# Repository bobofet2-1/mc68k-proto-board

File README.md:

# mc68k-proto-board
Code and design of legacy MC68000 proto board

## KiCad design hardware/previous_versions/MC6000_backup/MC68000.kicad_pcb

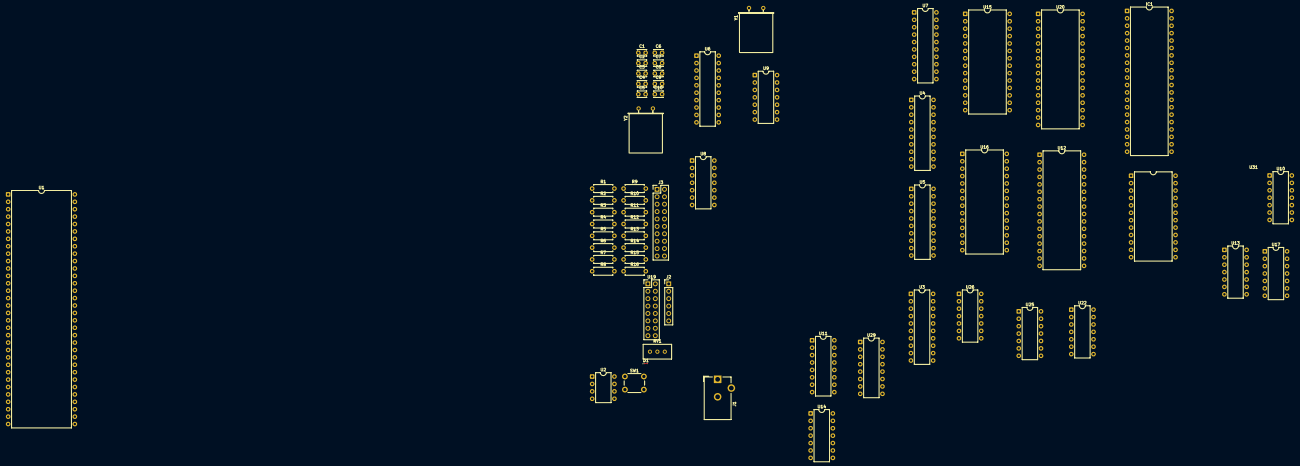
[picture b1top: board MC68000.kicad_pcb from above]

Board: 2 copper layers, 59 parts (0 on the bottom side), 146 nets, no tracks yet.

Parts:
C1: 10nF; C_Disc_D3.0mm_W2.0mm_P2.50mm
C2: 100n; C_Disc_D3.0mm_W2.0mm_P2.50mm
C3: 10n; C_Disc_D3.0mm_W2.0mm_P2.50mm
C4: 1u; C_Disc_D3.0mm_W2.0mm_P2.50mm
C5, C6, C7, C8: 15p; C_Disc_D3.0mm_W2.0mm_P2.50mm
C9: 10uF; C_Disc_D3.0mm_W2.0mm_P2.50mm
C10: 100nF; C_Disc_D3.0mm_W2.0mm_P2.50mm
D1: LED; LED_0201_0603Metric_Pad0.64x0.40mm_HandSolder
IC1: MC68681P; DIP-40_W15.24mm
J1: Conn_Coaxial_Power; BarrelJack_CUI_PJ-102AH_Horizontal
J2: FT232RL board; PinHeader_1x06_P2.54mm_Vertical
J3: DUART_OP_PORT; PinHeader_2x10_P2.54mm_Vertical
R1, R7, R9: 1M; R_Axial_DIN0207_L6.3mm_D2.5mm_P7.62mm_Horizontal
R2, R3, R4, R10, R11, R12, R13, R14, R15: 4.7K; R_Axial_DIN0207_L6.3mm_D2.5mm_P7.62mm_Horizontal
R5, R8: 470; R_Axial_DIN0207_L6.3mm_D2.5mm_P7.62mm_Horizontal
R6: 220; R_Axial_DIN0207_L6.3mm_D2.5mm_P7.62mm_Horizontal
R16: 10K; R_Axial_DIN0207_L6.3mm_D2.5mm_P7.62mm_Horizontal
RV1: 10K; Potentiometer_Bourns_3296W_Vertical
SW1: reset; SW_PUSH_6mm
U1: 68000D; DIP-64_W22.86mm
U2: LM555xN; DIP-8_W7.62mm
U3, U4, U5: 74LS373; DIP-20_W7.62mm
U6, U7: 74LS245; DIP-20_W7.62mm
U8, U17: 74LS32; DIP-14_W7.62mm
U9, U10: 74LS04; DIP-14_W7.62mm
U11, U29: 74LS138; DIP-16_W7.62mm
U12, U20: 628128_DIP32_SSOP32; DIP-32_W15.24mm
U13, U25, U26: 74LS00; DIP-14_W7.62mm
U14: 74LS08; DIP-14_W7.62mm
U15, U16: 28C256; DIP-28_W15.24mm
U19: EW20200YMY; PinHeader_2x08_P2.54mm_Vertical
U22: 74LS05; DIP-14_W7.62mm
U31: DS12887; DIP-24_W15.24mm
Y1: 16MHz; Crystal_HC49-U_Horizontal
Y2: 3.6864 MHz; Crystal_HC49-U_Horizontal

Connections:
+5V: C1.2, C9.1, C10.1, D1.2 (A), IC1.20 (VCC), IC1.21 (IRQ), IC1.37 (IACK), J1.1 (In), J2.4, J3.10, R1.1, R2.1, R3.1, R4.1, R5.1, R16.1, RV1.1, U1.14 (VCC), U1.49 (VCC), U2.4 (R), U2.8 (VCC), U3.20 (VCC), U4.18 (D7), U4.20 (VCC), U5.20 (VCC), U6.20 (VCC), U7.20 (VCC), U8.14 (VCC), U9.14 (VCC), U10.3, U10.5, U10.9, U10.11, U10.13, U10.14 (VCC), U11.6 (E3), U11.16 (VCC), U12.30 (CS2), U12.32 (VCC), U13.14 (VCC), U14.9, U14.10, U14.12, U14.13, U14.14 (VCC), U15.27 (~WE), U15.28 (VCC), U16.27 (~WE), U16.28 (VCC), U17.14 (VCC), U19.2 (VCC), U19.15 (VLED), U20.30 (CS2), U20.32 (VCC), U22.3, U22.5, U22.9, U22.11, U22.13, U22.14 (VCC), U25.14 (VCC), U26.9, U26.10, U26.12, U26.13, U26.14 (VCC), U29.6 (E3), U29.16 (VCC), U31.1 (MOT), U31.11 (RCLR), U31.12 (VCC)
/RAM_SELECT: U17.2, U25.11
/ROM_SELECT: U17.1, U26.3
BA1: IC1.1 (RS1), U3.2 (O0), U12.12 (A0), U15.10 (A0), U16.10 (A0), U19.4 (RS), U20.12 (A0)
BA2: IC1.3 (RS2), U3.5 (O1), U12.11 (A1), U15.9 (A1), U16.9 (A1), U20.11 (A1)
BA3: IC1.5 (RS3), U3.6 (O2), U12.10 (A2), U15.8 (A2), U16.8 (A2), U20.10 (A2)
BA4: IC1.6 (RS4), U3.9 (O3), U12.9 (A3), U15.7 (A3), U16.7 (A3), U20.9 (A3)
BA5: U3.12 (O4), U12.8 (A4), U15.6 (A4), U16.6 (A4), U20.8 (A4)
BA6: U3.15 (O5), U12.7 (A5), U15.5 (A5), U16.5 (A5), U20.7 (A5)
BA7: U3.16 (O6), U12.6 (A6), U15.4 (A6), U16.4 (A6), U20.6 (A6)
BA8: U3.19 (O7), U12.5 (A7), U15.3 (A7), U16.3 (A7), U20.5 (A7)
BA9: U5.2 (O0), U12.27 (A8), U15.25 (A8), U16.25 (A8), U20.27 (A8)
BA10: U5.5 (O1), U12.26 (A9), U15.24 (A9), U16.24 (A9), U20.26 (A9)
BA11: U5.6 (O2), U12.23 (A10), U15.21 (A10), U16.21 (A10), U20.23 (A10)
BA12: U5.9 (O3), U12.25 (A11), U15.23 (A11), U16.23 (A11), U20.25 (A11)
BA13: U5.12 (O4), U12.4 (A12), U15.2 (A12), U16.2 (A12), U20.4 (A12)
BA14: U5.15 (O5), U12.28 (A13), U15.26 (A13), U16.26 (A13), U20.28 (A13)
BA15: U5.16 (O6), U12.3 (A14), U15.1 (A14), U16.1 (A14), U20.3 (A14)
BA16: U5.19 (O7), U12.31 (A15), U20.31 (A15)
BA17: U4.2 (O0), U12.2 (A16), U20.2 (A16), U29.1 (A0)
BA18: U4.5 (O1), U29.2 (A1)
BA19: U4.6 (O2), U29.3 (A2)
BA21: U4.12 (O4), U11.1 (A0)
BA22: U4.15 (O5), U11.2 (A1)
BA23: U4.16 (O6), U11.3 (A2)
BD0: IC1.25 (D0), U6.18 (B0), U12.13 (Q0), U15.11 (D0)
BD1: IC1.16 (D1), U6.17 (B1), U12.14 (Q1), U15.12 (D1), U19.8 (DB1)
BD2: IC1.24 (D2), U6.16 (B2), U12.15 (Q2), U15.13 (D2), U19.9 (DB2)
BD3: IC1.17 (D3), U6.15 (B3), U12.17 (Q3), U15.15 (D3), U19.10 (DB3)
BD4: IC1.23 (D4), U6.14 (B4), U12.18 (Q4), U15.16 (D4), U19.11 (DB4)
BD5: IC1.18 (D5), U6.13 (B5), U12.19 (Q5), U15.17 (D5), U19.12 (DB5)
BD6: IC1.22 (D6), U6.12 (B6), U12.20 (Q6), U15.18 (D6), U19.13 (DB6)
BD7: IC1.19 (D7), U6.11 (B7), U12.21 (Q7), U15.19 (D7), U19.14 (DB7)
BD8: U7.18 (B0), U16.11 (D0), U20.13 (Q0), U31.15 (AD0)
BD9: U7.17 (B1), U16.12 (D1), U20.14 (Q1), U31.16 (AD1)
BD10: U7.16 (B2), U16.13 (D2), U20.15 (Q2), U31.17 (AD2)
BD11: U7.15 (B3), U16.15 (D3), U20.17 (Q3), U31.18 (AD3)
BD12: U7.14 (B4), U16.16 (D4), U20.18 (Q4), U31.19 (AD4)
BD13: U7.13 (B5), U16.17 (D5), U20.19 (Q5), U31.20 (AD5)
BD14: U7.12 (B6), U16.18 (D6), U20.20 (Q6), U31.21 (AD6)
BD15: U7.11 (B7), U16.19 (D7), U20.21 (Q7), U31.22 (AD7)
DUART_READY: U9.12, U17.4
GND: C1.1, C2.2, C3.2, C4.1, C4.2, C5.2, C6.2, C7.2, C8.2, C9.2, C10.2, IC1.40 (GND), J1.2 (Ext), J2.6, J3.9, R5.2, R10.1, R11.1, R12.1, R13.1, R14.1, R15.1, RV1.3, SW1.1, U1.16 (GND), U1.53 (GND), U2.1 (GND), U2.6 (THR), U2.7 (DIS), U3.1 (OE), U3.10 (GND), U4.1 (OE), U4.10 (GND), U5.1 (OE), U5.10 (GND), U6.10 (GND), U6.19 (CE), U7.10 (GND), U7.19 (CE), U8.7 (GND), U9.7 (GND), U10.7 (GND), U11.4 (E1), U11.8 (GND), U12.16 (GND), U12.24 (~OE), U13.7 (GND), U14.7 (GND), U15.14 (GND), U15.22 (~OE), U16.14 (GND), U16.22 (~OE), U17.7 (GND), U19.16 (VLSS), U20.16 (GND), U20.24 (~OE), U22.7 (GND), U25.7 (GND), U26.7 (GND), U29.4 (E1), U29.8 (GND), U31.14 (GND)
I/O: U11.11 (O4), U29.5 (E2)
LCD_READY: U17.5, U19.6 (E), U26.6
unnamed: C5.1, R7.1, U9.11, Y1.1
unnamed: C6.1, R8.2, Y1.2
unnamed: D1.1 (K), R6.1
unnamed: IC1.35 (CS), U14.6, U25.9
unnamed: IC1.9 (DTACK), U25.10
unnamed: IC1.7 (IP0), R10.2
unnamed: IC1.4 (IP1), R11.2
unnamed: IC1.36 (IP2), R12.2
unnamed: IC1.2 (IP3), R13.2
unnamed: IC1.39 (IP4), R14.2
unnamed: IC1.38 (IP5), R15.2
unnamed: IC1.29 (OP0), J3.1
unnamed: IC1.12 (OP1), J3.2
unnamed: IC1.28 (OP2), J3.3
unnamed: IC1.13 (OP3), J3.4
unnamed: IC1.27 (OP4), J3.5
unnamed: IC1.14 (OP5), J3.6
unnamed: IC1.26 (OP6), J3.7
unnamed: IC1.15 (OP7), J3.8
unnamed: IC1.31 (RXDA), J2.2
unnamed: IC1.10 (RXDB), R16.2
unnamed: IC1.30 (TXDA), J2.3
unnamed: C7.1, IC1.32 (X1/CLK), R9.1, Y2.1
unnamed: C8.1, IC1.33 (X2), R9.2, Y2.2
unnamed: R6.2, U22.2
unnamed: R7.2, R8.1, U9.9, U9.10
unnamed: U1.29 (A1), U3.3 (D0)
unnamed: U1.30 (A2), U3.4 (D1)
unnamed: U1.31 (A3), U3.7 (D2)
unnamed: U1.32 (A4), U3.8 (D3)
unnamed: U1.33 (A5), U3.13 (D4)
unnamed: U1.34 (A6), U3.14 (D5)
unnamed: U1.35 (A7), U3.17 (D6)
unnamed: U1.36 (A8), U3.18 (D7)
unnamed: U1.37 (A9), U5.3 (D0)
unnamed: U1.38 (A10), U5.4 (D1)
unnamed: U1.39 (A11), U5.7 (D2)
unnamed: U1.40 (A12), U5.8 (D3)
unnamed: U1.41 (A13), U5.13 (D4)
unnamed: U1.42 (A14), U5.14 (D5)
unnamed: U1.43 (A15), U5.17 (D6)
unnamed: U1.44 (A16), U5.18 (D7)
unnamed: U1.45 (A17), U4.3 (D0)
unnamed: U1.46 (A18), U4.4 (D1)
unnamed: U1.47 (A19), U4.7 (D2)
unnamed: U1.48 (A20), U4.8 (D3)
unnamed: U1.50 (A21), U4.13 (D4)
unnamed: U1.51 (A22), U4.14 (D5)
unnamed: U1.52 (A23), U4.17 (D6)
unnamed: U1.15 (CLK), U9.8
unnamed: U1.5 (D0), U6.2 (A0)
unnamed: U1.4 (D1), U6.3 (A1)
unnamed: U1.3 (D2), U6.4 (A2)
unnamed: U1.2 (D3), U6.5 (A3)
unnamed: U1.1 (D4), U6.6 (A4)
unnamed: U1.64 (D5), U6.7 (A5)
unnamed: U1.63 (D6), U6.8 (A6)
unnamed: U1.62 (D7), U6.9 (A7)
unnamed: U1.61 (D8), U7.2 (A0)
unnamed: U1.60 (D9), U7.3 (A1)
unnamed: U1.59 (D10), U7.4 (A2)
unnamed: U1.58 (D11), U7.5 (A3)
unnamed: U1.57 (D12), U7.6 (A4)
unnamed: U1.56 (D13), U7.7 (A5)
unnamed: U1.55 (D14), U7.8 (A6)
unnamed: U1.54 (D15), U7.9 (A7)
unnamed: R3.2, U1.17 (HALT), U9.4, U22.1
unnamed: C3.1, U2.5 (CV)
unnamed: U2.3 (Q), U9.3, U9.5
unnamed: C2.1, R1.2, SW1.2, U2.2 (TR)
unnamed: R2.2, U3.11 (LE), U4.11 (LE), U5.11 (LE)
unnamed: U6.1 (A->B), U8.3
unnamed: U7.1 (A->B), U8.6
unnamed: U8.2, U8.5, U9.2
unnamed: U10.2, U17.10
unnamed: U8.10, U8.13, U11.15 (O0)
unnamed: U11.7 (O7), U13.1, U14.2
unnamed: U8.9, U13.2, U13.6
unnamed: U8.12, U13.3, U13.4
unnamed: U8.8, U13.9, U13.12
unnamed: U8.11, U14.1
unnamed: U14.3, U25.2, U25.5
unnamed: U17.6, U17.9
unnamed: U17.3, U17.12
unnamed: U17.8, U17.13
unnamed: RV1.2, U19.3 (Vo)
unnamed: U9.13, U25.8
R/W: IC1.8 (R/~W), U1.9 (R/W), U9.1, U19.5 (R/W), U31.24 (R/W)
/AS: U1.6 (AS), U11.5 (E2), U31.2 (AS)
/CS_DUART: U14.4, U29.15 (O0)
/CS_LCD: U26.4, U29.14 (O1)
/CS_RAM_H: U13.11, U20.22 (~CS1), U25.13
/CS_RAM_L: U12.22 (~CS1), U13.8, U25.12
/CS_ROM_H: U16.20 (~CS), U25.6, U26.1
/CS_ROM_L: U15.20 (~CS), U25.3, U26.2
/CS_RTC: U10.1, U29.13 (O2), U31.23 (/CS)
/DTACK: U1.10 (DTACK), U17.11
/LDS: U1.8 (LDS), U8.1, U13.10, U14.5, U25.1, U26.5
/RESET: IC1.34 (RESET), R4.2, U1.18 (RESET), U9.6, U13.5
/UDS: U1.7 (UDS), U8.4, U13.13, U25.4, U31.3 (DS)
/WE_MEM: U12.29 (~WE), U20.29 (~WE)
